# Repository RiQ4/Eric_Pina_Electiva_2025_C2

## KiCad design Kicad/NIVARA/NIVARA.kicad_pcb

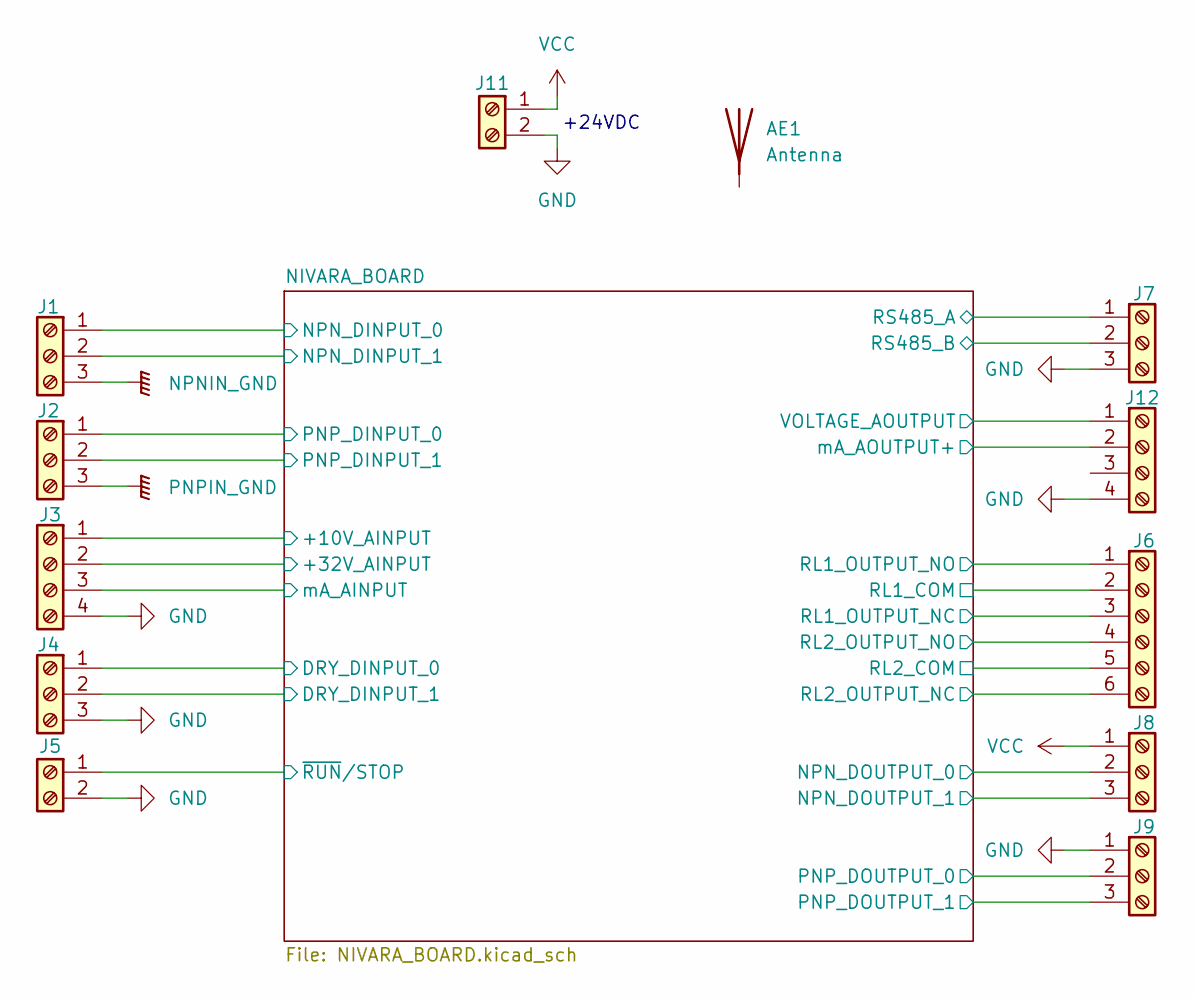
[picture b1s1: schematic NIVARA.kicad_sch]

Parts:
AE1: Antenna
J1, J2, J4, J7, J8, J9: Screw_Terminal_01x03; TerminalBlock_4Ucon_1x03_P3.50mm_Horizontal
J3, J12: Screw_Terminal_01x04; TerminalBlock_4Ucon_1x04_P3.50mm_Horizontal
J5, J11: Screw_Terminal_01x02; TerminalBlock_4Ucon_1x02_P3.50mm_Horizontal
J6: Screw_Terminal_01x06; TerminalBlock_4Ucon_1x06_P3.50mm_Horizontal

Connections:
/NIVARA_BOARD/+10V_AINPUT: J3.1; also elsewhere on the board
/NIVARA_BOARD/+32V_AINPUT: J3.2; also elsewhere on the board
/NIVARA_BOARD/DRY_DINPUT_0: J4.1; also elsewhere on the board
/NIVARA_BOARD/DRY_DINPUT_1: J4.2; also elsewhere on the board
/NIVARA_BOARD/NPN_DINPUT_0: J1.1; also elsewhere on the board
/NIVARA_BOARD/NPN_DINPUT_1: J1.2; also elsewhere on the board
/NIVARA_BOARD/NPN_DOUTPUT_0: J8.2; also elsewhere on the board
/NIVARA_BOARD/NPN_DOUTPUT_1: J8.3; also elsewhere on the board
/NIVARA_BOARD/PNP_DINPUT_0: J2.1; also elsewhere on the board
/NIVARA_BOARD/PNP_DINPUT_1: J2.2; also elsewhere on the board
/NIVARA_BOARD/PNP_DOUTPUT_0: J9.2; also elsewhere on the board
/NIVARA_BOARD/PNP_DOUTPUT_1: J9.3; also elsewhere on the board
/NIVARA_BOARD/RL1_COM: J6.2; also elsewhere on the board
/NIVARA_BOARD/RL1_OUTPUT_NC: J6.3; also elsewhere on the board
/NIVARA_BOARD/RL1_OUTPUT_NO: J6.1; also elsewhere on the board
/NIVARA_BOARD/RL2_COM: J6.5; also elsewhere on the board
/NIVARA_BOARD/RL2_OUTPUT_NC: J6.6; also elsewhere on the board
/NIVARA_BOARD/RL2_OUTPUT_NO: J6.4; also elsewhere on the board
/NIVARA_BOARD/RS485_A: J7.1; also elsewhere on the board
/NIVARA_BOARD/RS485_B: J7.2; also elsewhere on the board
/NIVARA_BOARD/VOLTAGE_AOUTPUT: J12.1; also elsewhere on the board
/NIVARA_BOARD/mA_AINPUT: J3.3; also elsewhere on the board
/NIVARA_BOARD/mA_AOUTPUT+: J12.2; also elsewhere on the board
/NIVARA_BOARD/~RUN/STOP: J5.1; also elsewhere on the board
GND: J3.4, J4.3, J5.2, J7.3, J9.1, J11.2, J12.4; also elsewhere on the board
NPNIN_GND: J1.3; also elsewhere on the board
PNPIN_GND: J2.3; also elsewhere on the board
VCC: J8.1, J11.1; also elsewhere on the board

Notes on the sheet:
+24VDC

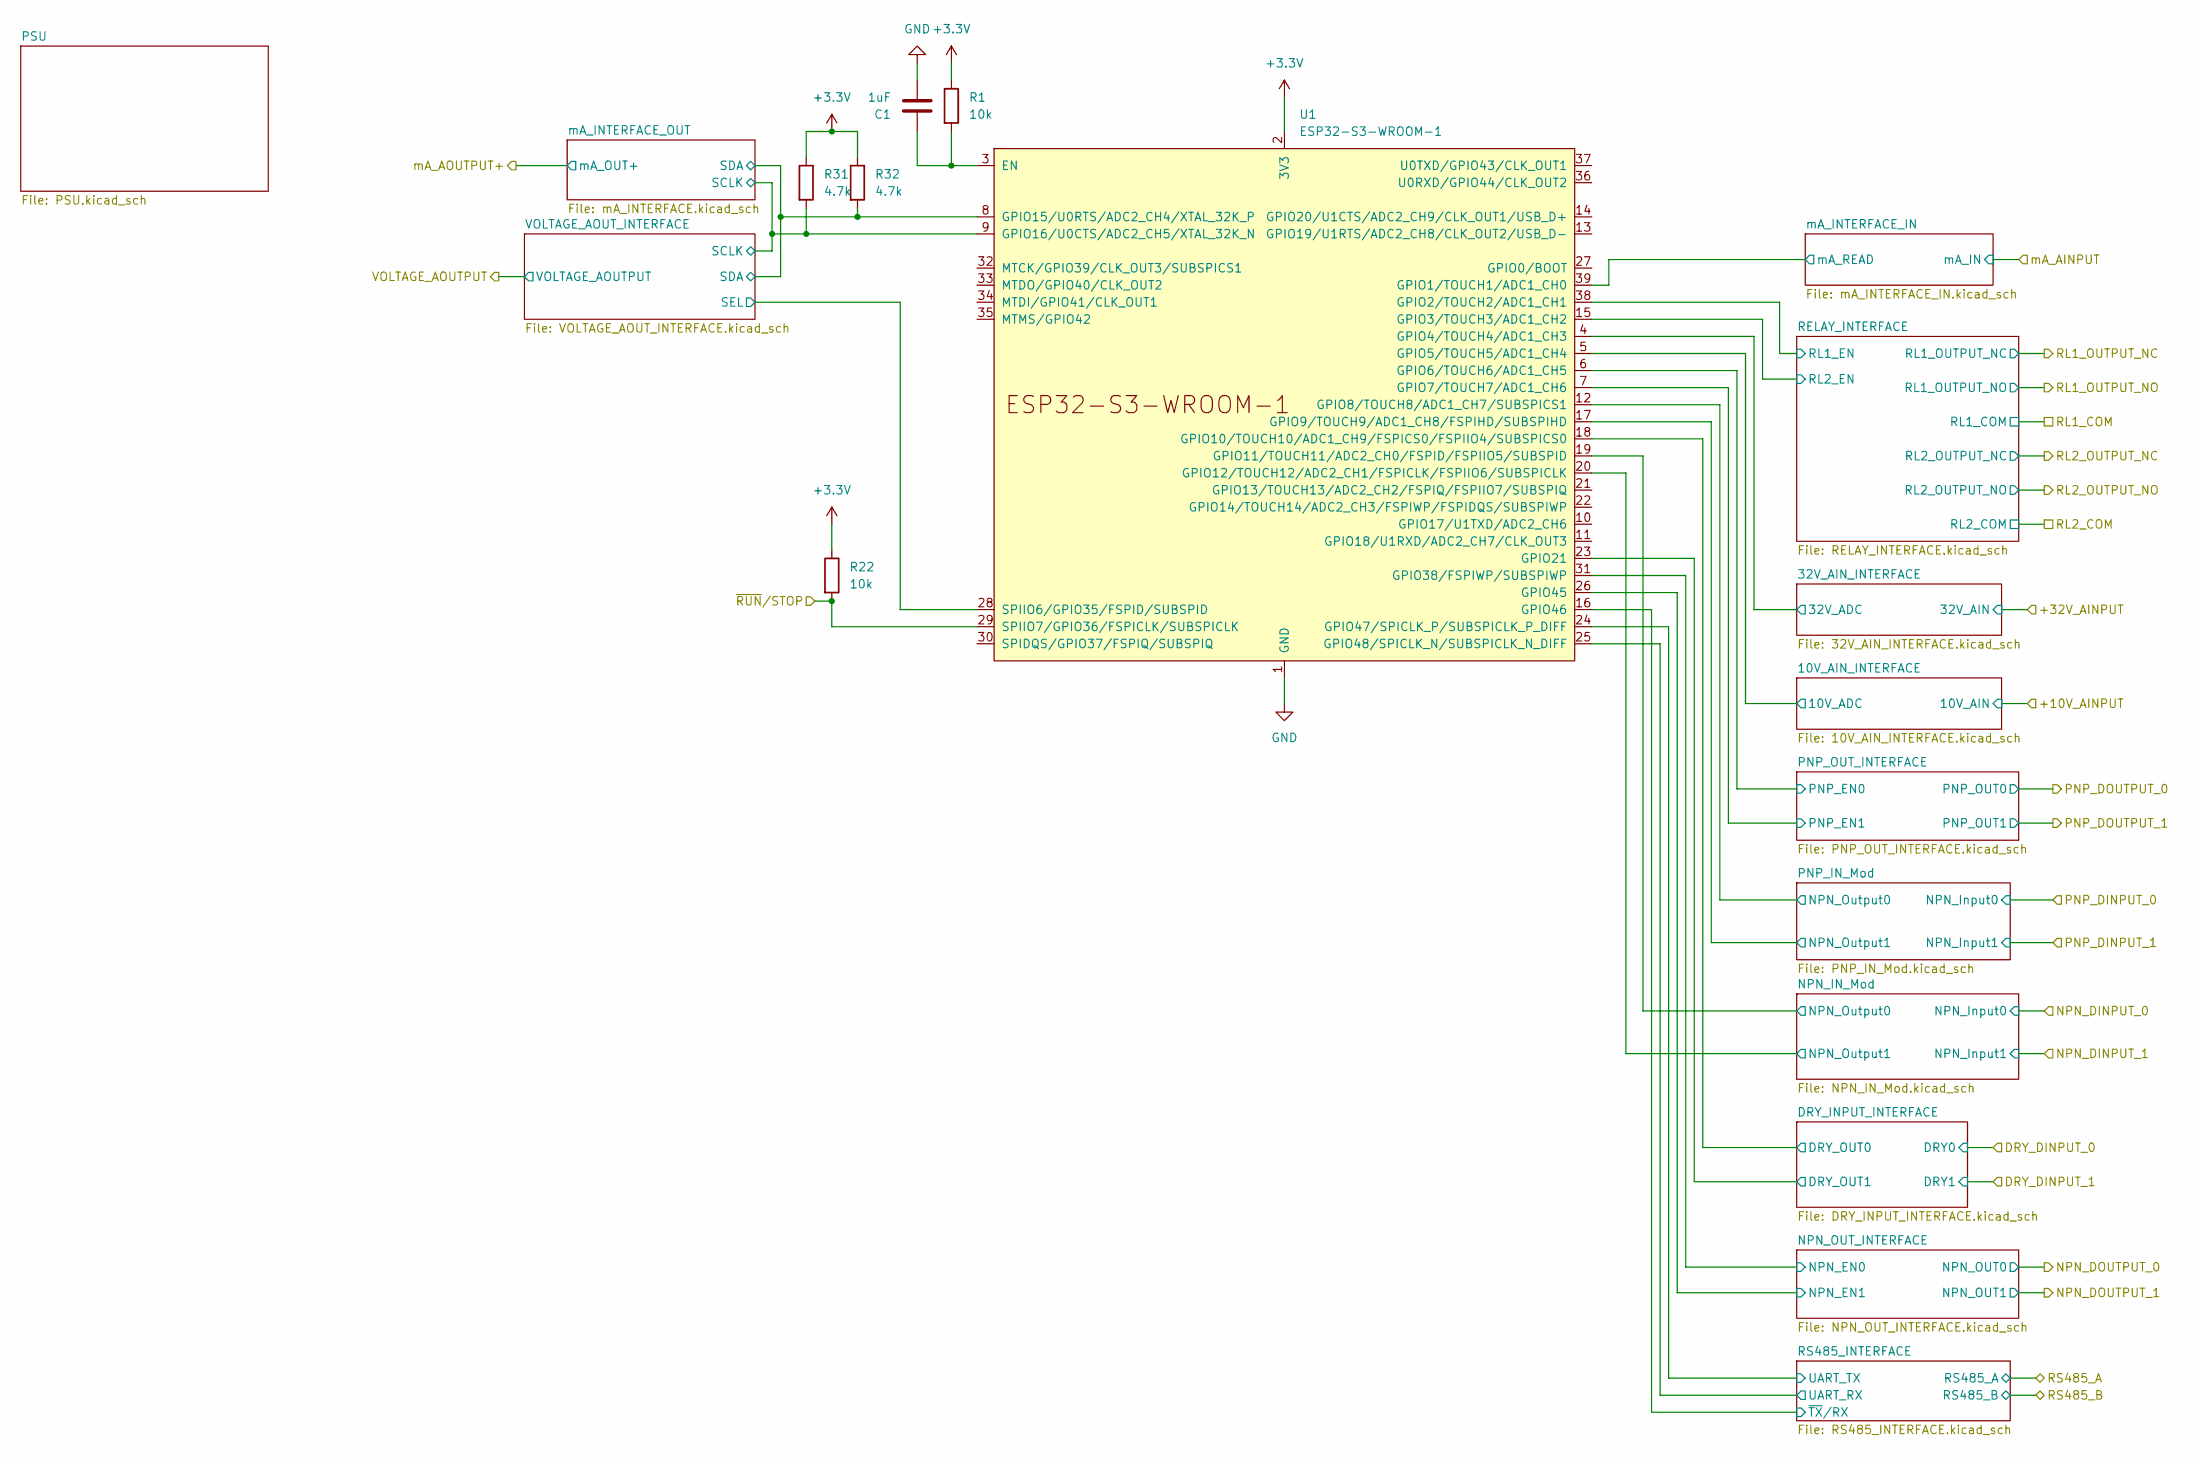
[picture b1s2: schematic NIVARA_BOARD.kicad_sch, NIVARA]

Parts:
C1: 1uF; C_0603_1608Metric
R1, R22: 10k; R_0603_1608Metric
R31, R32: 4.7k; R_0603_1608Metric
U1: ESP32-S3-WROOM-1

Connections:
+3.3V: R1.1, R22.1, R31.1, R32.1, U1.2 (3V3); also elsewhere on the board
/NIVARA_BOARD/10V_AIN_INTERFACE/10V_ADC: U1.5 (GPIO5/TOUCH5/ADC1_CH4); also elsewhere on the board
/NIVARA_BOARD/32V_AIN_INTERFACE/32V_ADC: U1.4 (GPIO4/TOUCH4/ADC1_CH3); also elsewhere on the board
/NIVARA_BOARD/DRY_INPUT_INTERFACE/DRY_OUT0: U1.18 (GPIO10/TOUCH10/ADC1_CH9/FSPICS0/FSPIIO4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); also elsewhere on the board
/NIVARA_BOARD/DRY_INPUT_INTERFACE/DRY_OUT1: U1.23 (GPIO21); also elsewhere on the board
/NIVARA_BOARD/NPN_IN_Mod/NPN_Output0: U1.19 (GPIO11/TOUCH11/ADC2_CH0/FSPID/FSPIIO5/S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); also elsewhere on the board
/NIVARA_BOARD/NPN_IN_Mod/NPN_Output1: U1.20 (GPIO12/TOUCH12/ADC2_CH1/FSPICLK/FSPIIO6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); also elsewhere on the board
/NIVARA_BOARD/NPN_OUT_INTERFACE/NPN_EN0: U1.31 (GPIO38/FSPIWP/SUBSPIWP); also elsewhere on the board
/NIVARA_BOARD/NPN_OUT_INTERFACE/NPN_EN1: U1.26 (GPIO45); also elsewhere on the board
/NIVARA_BOARD/PNP_IN_Mod/NPN_Output0: U1.12 (GPIO8/TOUCH8/ADC1_CH7/SUBSPICS1); also elsewhere on the board
/NIVARA_BOARD/PNP_IN_Mod/NPN_Output1: U1.17 (GPIO9/TOUCH9/ADC1_CH8/FSPIHD/SUBSPIHD); also elsewhere on the board
/NIVARA_BOARD/PNP_OUT_INTERFACE/PNP_EN0: U1.6 (GPIO6/TOUCH6/ADC1_CH5); also elsewhere on the board
/NIVARA_BOARD/PNP_OUT_INTERFACE/PNP_EN1: U1.7 (GPIO7/TOUCH7/ADC1_CH6); also elsewhere on the board
/NIVARA_BOARD/RELAY_INTERFACE/RL1_EN: U1.38 (GPIO2/TOUCH2/ADC1_CH1); also elsewhere on the board
/NIVARA_BOARD/RELAY_INTERFACE/RL2_EN: U1.15 (GPIO3/TOUCH3/ADC1_CH2); also elsewhere on the board
/NIVARA_BOARD/RS485_INTERFACE/UART_RX: U1.25 (GPIO48/SPICLK_N/SUBSPICLK_N_DIFF); also elsewhere on the board
/NIVARA_BOARD/RS485_INTERFACE/UART_TX: U1.24 (GPIO47/SPICLK_P/SUBSPICLK_P_DIFF); also elsewhere on the board
/NIVARA_BOARD/RS485_INTERFACE/~TX/RX: U1.16 (GPIO46); also elsewhere on the board
/NIVARA_BOARD/VOLTAGE_AOUT_INTERFACE/SCLK: R31.2, U1.9 (GPIO16/U0CTS/ADC2_CH5/XTAL_32K_N); also elsewhere on the board
/NIVARA_BOARD/VOLTAGE_AOUT_INTERFACE/SDA: R32.2, U1.8 (GPIO15/U0RTS/ADC2_CH4/XTAL_32K_P); also elsewhere on the board
/NIVARA_BOARD/VOLTAGE_AOUT_INTERFACE/SEL: U1.28 (SPIIO6/GPIO35/FSPID/SUBSPID); also elsewhere on the board
/NIVARA_BOARD/mA_AINPUT: U1.39 (GPIO1/TOUCH1/ADC1_CH0); also elsewhere on the board
/NIVARA_BOARD/~RUN/STOP: R22.2, U1.29 (SPIIO7/GPIO36/FSPICLK/SUBSPICLK); also elsewhere on the board
GND: C1.2, U1.1 (GND), U1.40 (GND), U1.41 (GND); also elsewhere on the board
unnamed: C1.1, R1.2, U1.3 (EN)

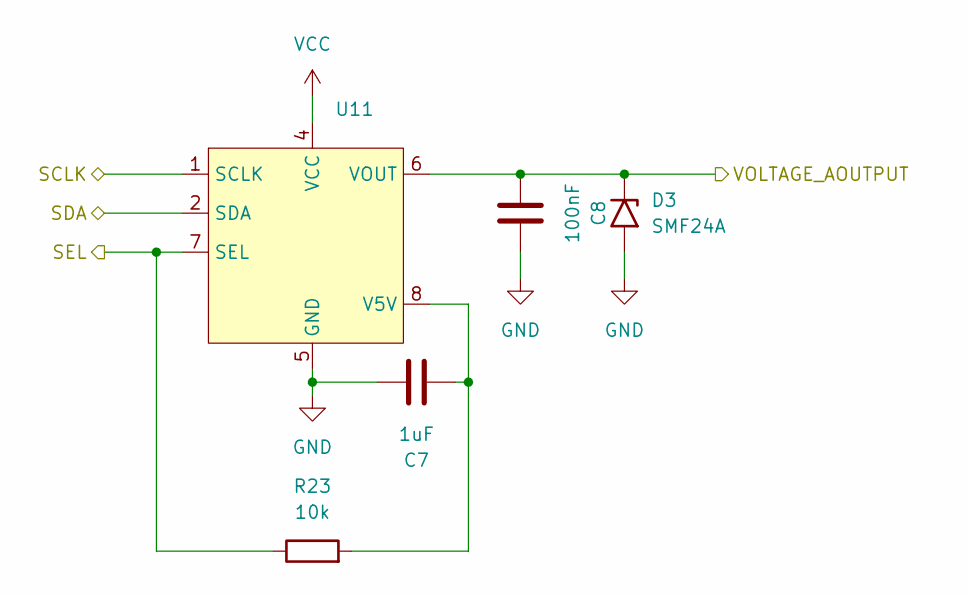
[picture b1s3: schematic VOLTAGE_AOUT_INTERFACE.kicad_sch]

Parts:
C7: 1uF; C_0603_1608Metric
C8: 100nF; C_0603_1608Metric
D3: SMF24A; D_SMF; LCSC# C7495269
R23: 10k; R_0603_1608Metric
U11: eSOP-8

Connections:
/NIVARA_BOARD/VOLTAGE_AOUTPUT: C8.2, D3.1 (A1), U11.6 (VOUT); also elsewhere on the board
/NIVARA_BOARD/VOLTAGE_AOUT_INTERFACE/SCLK: U11.1 (SCLK); also elsewhere on the board
/NIVARA_BOARD/VOLTAGE_AOUT_INTERFACE/SDA: U11.2 (SDA); also elsewhere on the board
/NIVARA_BOARD/VOLTAGE_AOUT_INTERFACE/SEL: R23.1, U11.7 (SEL); also elsewhere on the board
GND: C7.1, C8.1, D3.2 (A2), U11.5 (GND); also elsewhere on the board
unnamed: C7.2, R23.2, U11.8 (V5V)
VCC: U11.4 (VCC); also elsewhere on the board

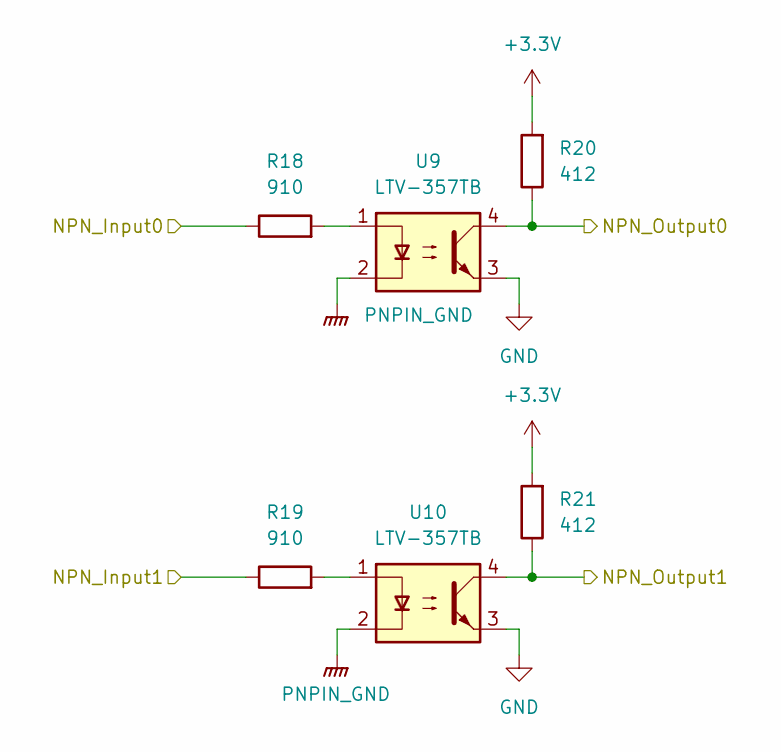
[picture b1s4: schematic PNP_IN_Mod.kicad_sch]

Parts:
R18, R19: 910; R_0603_1608Metric; LCSC# C114670
R20, R21: 412; R_0603_1608Metric
U9, U10: LTV-357TB; SO-4_4.4x3.6mm_P2.54mm

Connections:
+3.3V: R20.2, R21.2; also elsewhere on the board
/NIVARA_BOARD/PNP_DINPUT_0: R18.1; also elsewhere on the board
/NIVARA_BOARD/PNP_DINPUT_1: R19.1; also elsewhere on the board
/NIVARA_BOARD/PNP_IN_Mod/NPN_Output0: R20.1, U9.4; also elsewhere on the board
/NIVARA_BOARD/PNP_IN_Mod/NPN_Output1: R21.1, U10.4; also elsewhere on the board
GND: U9.3, U10.3; also elsewhere on the board
unnamed: R18.2, U9.1
unnamed: R19.2, U10.1
PNPIN_GND: U9.2, U10.2; also elsewhere on the board

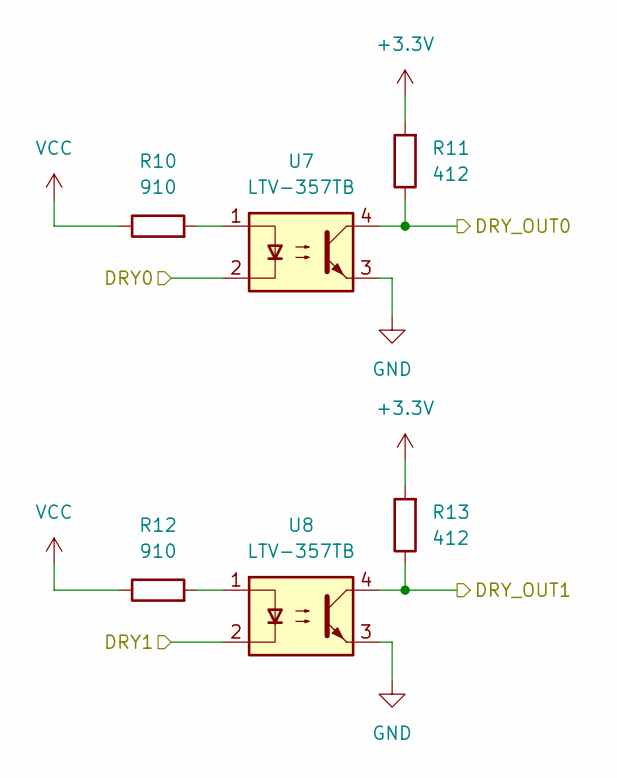
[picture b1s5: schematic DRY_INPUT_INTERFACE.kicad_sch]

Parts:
R10, R12: 910; R_0603_1608Metric; LCSC# C114670
R11, R13: 412; R_0603_1608Metric
U7, U8: LTV-357TB; SO-4_4.4x3.6mm_P2.54mm

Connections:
+3.3V: R11.2, R13.2; also elsewhere on the board
/NIVARA_BOARD/DRY_DINPUT_0: U7.2; also elsewhere on the board
/NIVARA_BOARD/DRY_DINPUT_1: U8.2; also elsewhere on the board
/NIVARA_BOARD/DRY_INPUT_INTERFACE/DRY_OUT0: R11.1, U7.4; also elsewhere on the board
/NIVARA_BOARD/DRY_INPUT_INTERFACE/DRY_OUT1: R13.1, U8.4; also elsewhere on the board
GND: U7.3, U8.3; also elsewhere on the board
unnamed: R10.2, U7.1
unnamed: R12.2, U8.1
VCC: R10.1, R12.1; also elsewhere on the board

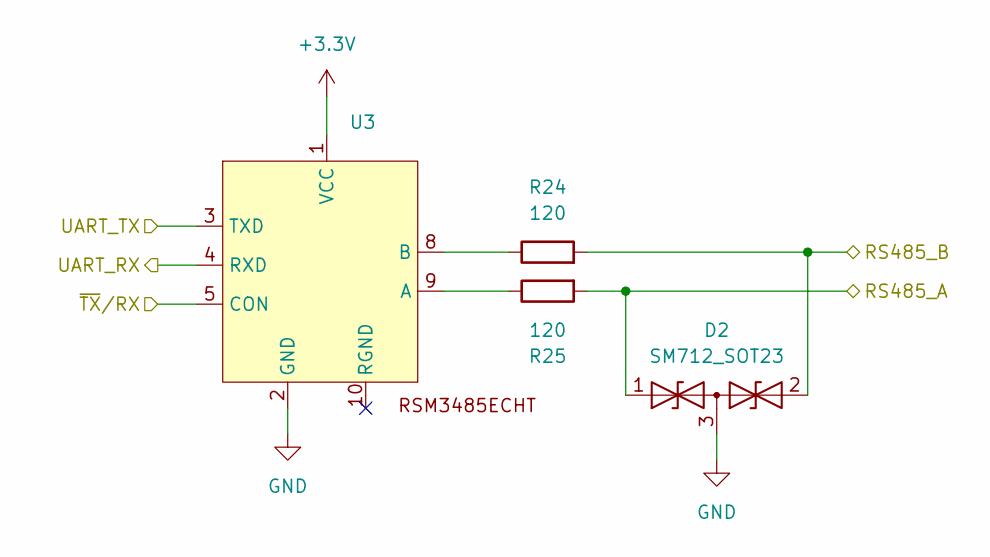
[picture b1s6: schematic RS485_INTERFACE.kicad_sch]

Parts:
D2: SM712_SOT23; SOT-23
R24, R25: 120; R_0603_1608Metric
U3: YLPTEC RSM3485ECHT

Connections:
+3.3V: U3.1 (VCC); also elsewhere on the board
/NIVARA_BOARD/RS485_A: D2.1 (A1), R25.2; also elsewhere on the board
/NIVARA_BOARD/RS485_B: D2.2 (A2), R24.2; also elsewhere on the board
/NIVARA_BOARD/RS485_INTERFACE/UART_RX: U3.4 (RXD); also elsewhere on the board
/NIVARA_BOARD/RS485_INTERFACE/UART_TX: U3.3 (TXD); also elsewhere on the board
/NIVARA_BOARD/RS485_INTERFACE/~TX/RX: U3.5 (CON); also elsewhere on the board
GND: D2.3 (common), U3.2 (GND); also elsewhere on the board
unnamed: R25.1, U3.9 (A)
unnamed: R24.1, U3.8 (B)

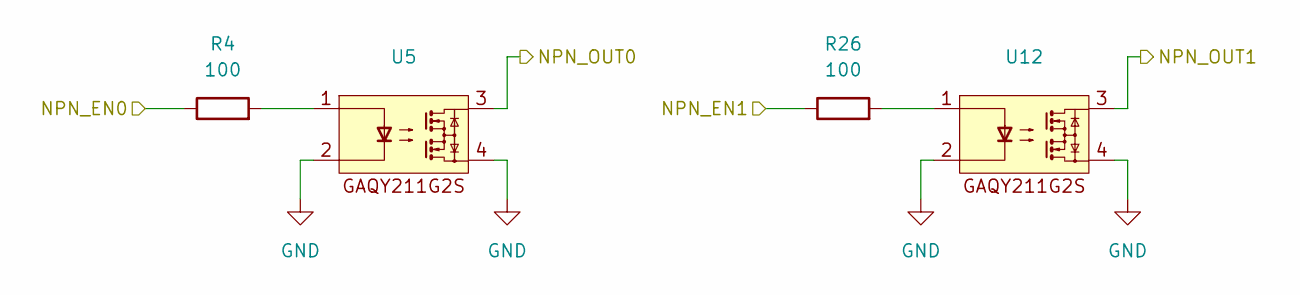
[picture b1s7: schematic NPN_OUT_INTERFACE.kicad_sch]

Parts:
R4, R26: 100; R_0603_1608Metric
U5, U12: SO-4_4.4x4.3mm_P2.54mm

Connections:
/NIVARA_BOARD/NPN_DOUTPUT_0: U5.3; also elsewhere on the board
/NIVARA_BOARD/NPN_DOUTPUT_1: U12.3; also elsewhere on the board
/NIVARA_BOARD/NPN_OUT_INTERFACE/NPN_EN0: R4.1; also elsewhere on the board
/NIVARA_BOARD/NPN_OUT_INTERFACE/NPN_EN1: R26.1; also elsewhere on the board
GND: U5.2, U5.4, U12.2, U12.4; also elsewhere on the board
unnamed: R4.2, U5.1
unnamed: R26.2, U12.1

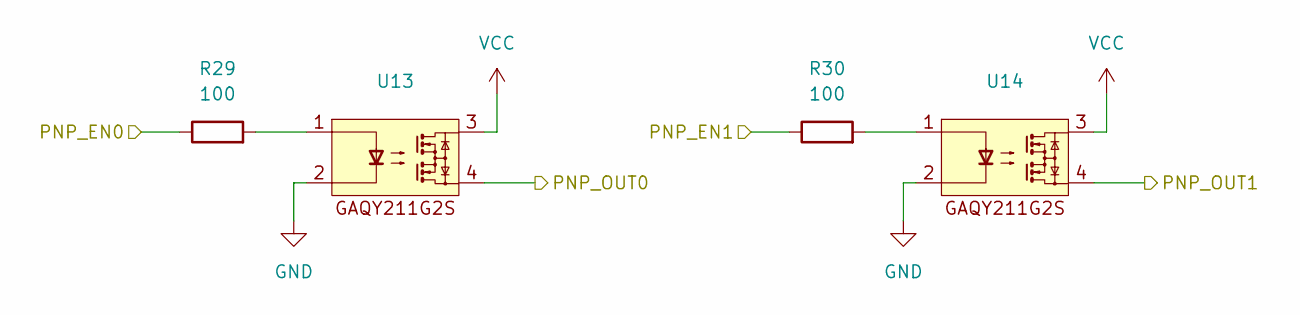
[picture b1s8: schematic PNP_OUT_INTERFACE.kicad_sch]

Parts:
R29, R30: 100; R_0603_1608Metric
U13, U14: SO-4_4.4x4.3mm_P2.54mm

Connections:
/NIVARA_BOARD/PNP_DOUTPUT_0: U13.4; also elsewhere on the board
/NIVARA_BOARD/PNP_DOUTPUT_1: U14.4; also elsewhere on the board
/NIVARA_BOARD/PNP_OUT_INTERFACE/PNP_EN0: R29.1; also elsewhere on the board
/NIVARA_BOARD/PNP_OUT_INTERFACE/PNP_EN1: R30.1; also elsewhere on the board
GND: U13.2, U14.2; also elsewhere on the board
unnamed: R29.2, U13.1
unnamed: R30.2, U14.1
VCC: U13.3, U14.3; also elsewhere on the board

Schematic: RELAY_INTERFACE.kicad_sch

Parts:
K1, K2: TQ2-24V; TQ2=24V; PARTREV 201911
Q2: SOT-363_SC-70-6; LCSC# C2984831

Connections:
/NIVARA_BOARD/RELAY_INTERFACE/RL1_EN: Q2.3 (1B); also elsewhere on the board
/NIVARA_BOARD/RELAY_INTERFACE/RL2_EN: Q2.4 (2B); also elsewhere on the board
/NIVARA_BOARD/RL1_COM: K1.3, K1.8; also elsewhere on the board
/NIVARA_BOARD/RL1_OUTPUT_NC: K1.2, K1.9; also elsewhere on the board
/NIVARA_BOARD/RL1_OUTPUT_NO: K1.4, K1.7; also elsewhere on the board
/NIVARA_BOARD/RL2_COM: K2.3, K2.8; also elsewhere on the board
/NIVARA_BOARD/RL2_OUTPUT_NC: K2.2, K2.9; also elsewhere on the board
/NIVARA_BOARD/RL2_OUTPUT_NO: K2.4, K2.7; also elsewhere on the board
GND: Q2.2 (E); also elsewhere on the board
unnamed: K1.10, Q2.1 (1C)
unnamed: K2.10, Q2.6 (2C)
VCC: K1.1, K2.1, Q2.5 (COM); also elsewhere on the board

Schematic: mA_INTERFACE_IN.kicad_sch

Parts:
C11: 100nF; C_0603_1608Metric
R8: 120; R_0603_1608Metric; Tolerance 0.1-1%

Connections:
/NIVARA_BOARD/mA_AINPUT: C11.1, R8.2; also elsewhere on the board
GND: C11.2, R8.1; also elsewhere on the board

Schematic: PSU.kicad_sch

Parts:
C2: 100nF; C_0603_1608Metric
C3: 10uF; C_0603_1608Metric; Voltage 50V
C4, C5: 22uF; C_0603_1608Metric
C6: 100pF; C_0603_1608Metric
D6, D7: SMF24A; D_SMF
JP1: SolderJumper_2_Open; SolderJumper-2_P1.3mm_Open_RoundedPad1.0x1.5mm
L1: 6.8uH; L_6.3x6.3_H3
R2: 196k; R_0603_1608Metric
R3: 62k; R_0603_1608Metric
U2: AP63200WU; TSOT-23-6

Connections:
+3.3V: JP1.2 (B); also elsewhere on the board
GND: C3.1, C4.1, C5.1, D6.2 (A2), D7.2 (A2), R3.2, U2.4 (GND); also elsewhere on the board
unnamed: C4.2, C5.2, C6.1, D6.1 (A1), JP1.1 (A), L1.2, R2.1
unnamed: C2.1, U2.6 (BST)
unnamed: C6.2, R2.2, R3.1, U2.1 (FB)
unnamed: C2.2, L1.1, U2.5 (SW)
VCC: C3.2, D7.1 (A1), U2.2 (EN), U2.3 (IN); also elsewhere on the board

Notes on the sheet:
DO NOT MOUNT FOR AP63203: C6 R3 SUBSITUTE: R2 -> 0Ohm L -> 3.9uH
AP63200/AP63201 OR AP63203

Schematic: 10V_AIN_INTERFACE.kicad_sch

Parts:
C10: 100nF; C_0603_1608Metric
R16: 51k; R_0603_1608Metric
R17: 16k; R_0603_1608Metric

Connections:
/NIVARA_BOARD/10V_AIN_INTERFACE/10V_ADC: C10.1, R16.2, R17.1; also elsewhere on the board
/NIVARA_BOARD/+10V_AINPUT: R16.1; also elsewhere on the board
GND: C10.2, R17.2; also elsewhere on the board

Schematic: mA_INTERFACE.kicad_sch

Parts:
C12: 220pF; C_0603_1608Metric
C13, C14: 1uF; C_0603_1608Metric
C15: 100nF; C_0603_1608Metric
D1: D_Zener
D4: 1N4007; D_DO-41_SOD81_P10.16mm_Horizontal
D5: SMF24A; D_SMF
JP2, JP3, JP4: SolderJumper_2_Open; SolderJumper-2_P1.3mm_Open_RoundedPad1.0x1.5mm
R6: 2.5k; R_0603_1608Metric
R27: 100k; R_0603_1608Metric
R28: 15; R_0603_1608Metric
R33, R34, R35: 10k; R_0603_1608Metric
T1: IRF9310TRPBF; SO-8
U6: SSOP-10-1EP_3.9x4.9mm_P1mm_EP2.1x3.3mm

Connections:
/NIVARA_BOARD/VOLTAGE_AOUT_INTERFACE/SCLK: U6.1 (SCLK); also elsewhere on the board
/NIVARA_BOARD/VOLTAGE_AOUT_INTERFACE/SDA: U6.2 (SDA); also elsewhere on the board
/NIVARA_BOARD/mA_AOUTPUT+: D4.1 (K); also elsewhere on the board
GND: C12.2, C13.2, C14.2, C15.2, D5.2 (A2), JP2.1 (A), JP3.1 (A), JP3.2 (B), JP4.1 (A), JP4.2 (B), R6.2, R27.2, R34.2, R35.2, U6.4 (A1), U6.6 (GND), U6.9 (A2); also elsewhere on the board
unnamed: C14.1, D1.2 (A), R27.1, T1.4
unnamed: D4.2 (A), R28.2
unnamed: C15.1, D5.1 (A1), R28.1, T1.5, T1.6, T1.7, T1.8
unnamed: JP2.2 (B), R33.2, U6.3 (A0)
unnamed: T1.1, T1.2, T1.3, U6.8 (IOUT)
unnamed: C12.1, R6.1, U6.7 (SET)
unnamed: C13.1, R33.1, R34.1, R35.1, U6.10 (V5V)
VCC: D1.1 (K), U6.5 (VCC); also elsewhere on the board

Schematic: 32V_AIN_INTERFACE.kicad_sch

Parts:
C9: 100nF; C_0603_1608Metric
R14: 160k; R_0603_1608Metric
R15: 13k; R_0603_1608Metric

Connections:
/NIVARA_BOARD/32V_AIN_INTERFACE/32V_ADC: C9.1, R14.2, R15.1; also elsewhere on the board
/NIVARA_BOARD/+32V_AINPUT: R14.1; also elsewhere on the board
GND: C9.2, R15.2; also elsewhere on the board

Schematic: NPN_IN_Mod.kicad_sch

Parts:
R5, R9: 412; R_0603_1608Metric
R7, R36: 910; R_0603_1608Metric; LCSC# C114670
U4, U15: LTV-357TB; SO-4_4.4x3.6mm_P2.54mm

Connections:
+3.3V: R5.2, R9.2; also elsewhere on the board
/NIVARA_BOARD/NPN_DINPUT_0: R36.1; also elsewhere on the board
/NIVARA_BOARD/NPN_DINPUT_1: R7.1; also elsewhere on the board
/NIVARA_BOARD/NPN_IN_Mod/NPN_Output0: R5.1, U15.4; also elsewhere on the board
/NIVARA_BOARD/NPN_IN_Mod/NPN_Output1: R9.1, U4.4; also elsewhere on the board
GND: U4.3, U15.3; also elsewhere on the board
NPNIN_GND: U4.2, U15.2; also elsewhere on the board
unnamed: R7.2, U4.1
unnamed: R36.2, U15.1

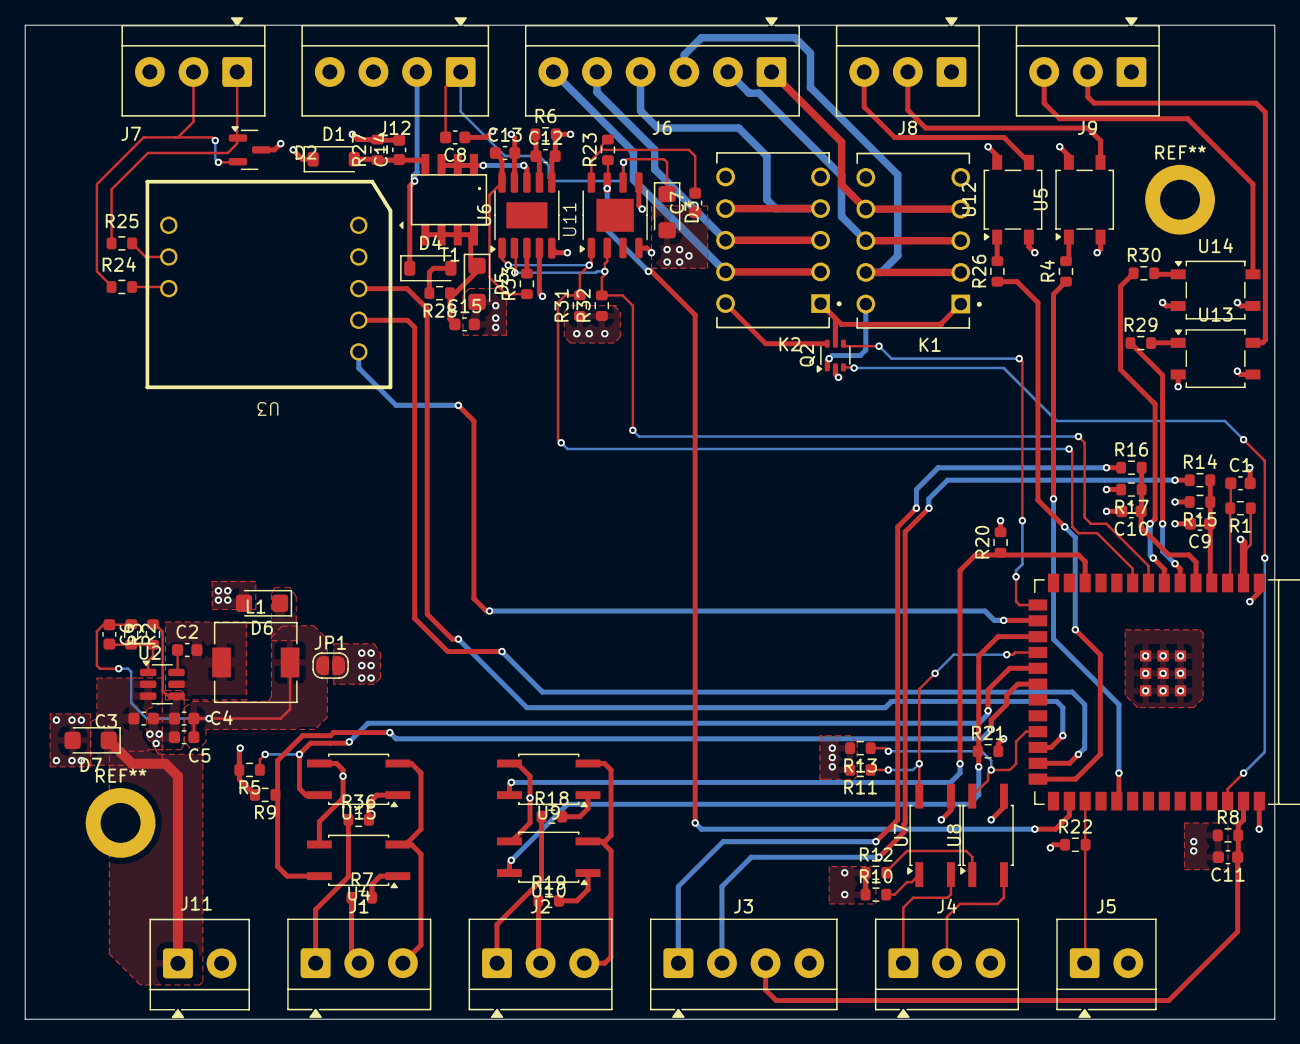
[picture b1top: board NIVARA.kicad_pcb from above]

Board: 4 copper layers, 100.2 x 79.8 mm, 88 parts (0 on the bottom side), 76 nets.

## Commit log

2025-06-05 Diseños en programas CAD
2025-06-06 Garabato NIVARA
2025-06-13 KiCAD Files
    Creación del Proyecto en KiCAD
2025-06-13 Hierarchical Design In KiCAD
2025-06-13 Hierarchical Labels added
2025-06-14 Initial Capture Finished
2025-06-14 Wrapping up for today :3
2025-06-17 Solder Jumper
    Para que no me pase lo mismo de mi proyecto
2025-06-21 RS-485 Update
    RS-485 Isolated circuit updated. Created new symbol and footprint for the YLPTEC RSM3485ECHT IC.
2025-06-22 Silly little things
2025-06-23 Relay Interface
    Progress made with the Relay Interface.
2025-06-23 Silly little things
    Rookie mistake
2025-06-23 Added Datasheets
2025-07-12 Rutinario
2025-07-13 Documento de Requisitos
2025-07-15 INVESTIGACIÓN MBSE
2025-07-16 FULL SCHEMATIC!!111!!!
    Dik
2025-07-16 tengo sueño
    Hay que dormir
2025-08-15 Debí de enrutar antes :C
    tengo sueño
2025-08-16 casi casi
2025-08-22 Faltan dos Cositas
    Casi terminamos de enrutar
2025-08-22 casi terminamos de enrutar
2025-08-22 ayuda
2025-08-22 FINAL?
